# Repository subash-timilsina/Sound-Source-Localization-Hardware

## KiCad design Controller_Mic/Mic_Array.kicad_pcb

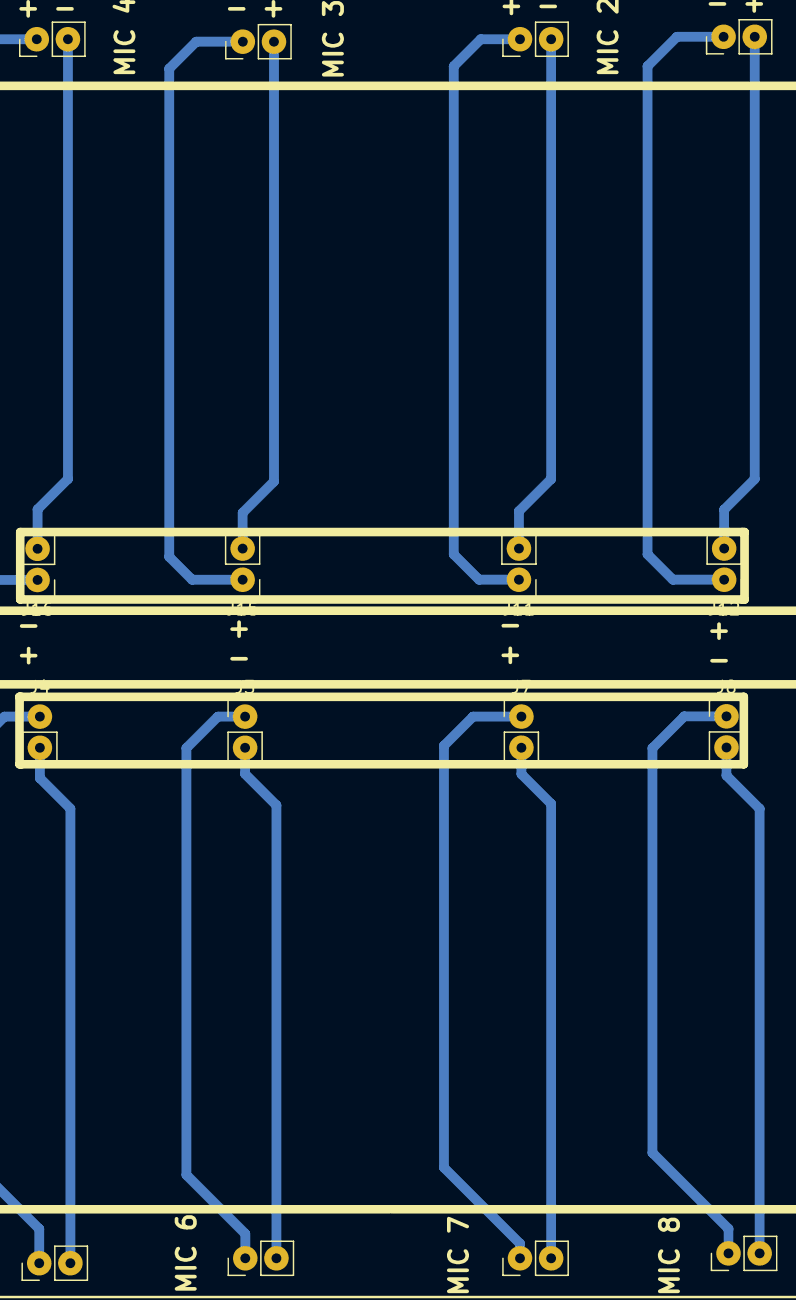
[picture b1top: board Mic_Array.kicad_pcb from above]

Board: 2 copper layers, 16 parts (0 on the bottom side), 16 nets.

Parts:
J1, J9: Mic2; Pin_Header_Straight_1x02_Pitch2.54mm
J2, J10: Mic1; Pin_Header_Straight_1x02_Pitch2.54mm
J3, J11: Mic2_chip; Pin_Header_Straight_1x02_Pitch2.54mm
J4, J12: Mic1_chip; Pin_Header_Straight_1x02_Pitch2.54mm
J5, J13: Mic4; Pin_Header_Straight_1x02_Pitch2.54mm
J6, J14: Mic3; Pin_Header_Straight_1x02_Pitch2.54mm
J7, J15: Mic4_chip; Pin_Header_Straight_1x02_Pitch2.54mm
J8, J16: Mic3_chip; Pin_Header_Straight_1x02_Pitch2.54mm

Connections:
unnamed: J1.1, J3.1
unnamed: J1.2, J3.2
unnamed: J2.1, J4.1
unnamed: J2.2, J4.2
unnamed: J5.1, J7.1
unnamed: J5.2, J7.2
unnamed: J6.1, J8.1
unnamed: J6.2, J8.2
unnamed: J10.1, J12.1
unnamed: J10.2, J12.2
unnamed: J9.1, J11.1
unnamed: J9.2, J11.2
unnamed: J13.1, J15.1
unnamed: J13.2, J15.2
unnamed: J14.1, J16.1
unnamed: J14.2, J16.2

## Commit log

2019-07-21 Hardware part of SSL
2019-07-28 New updates on data transfer
2019-07-28 New changes on data transmission
2022-04-15 Create LICENSE
